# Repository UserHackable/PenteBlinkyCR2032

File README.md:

## PentaBlinkyCR2032 

### Board dimensions

* (130000, 150000) original units
* (1.3000, 1.5000) inches
* (33.0200, 38.1000) mm

[gerbers](PentaBlinkyCR2032_gerber.zip?raw=true)

| Front | Back |
| --- | --- |
|  |  |

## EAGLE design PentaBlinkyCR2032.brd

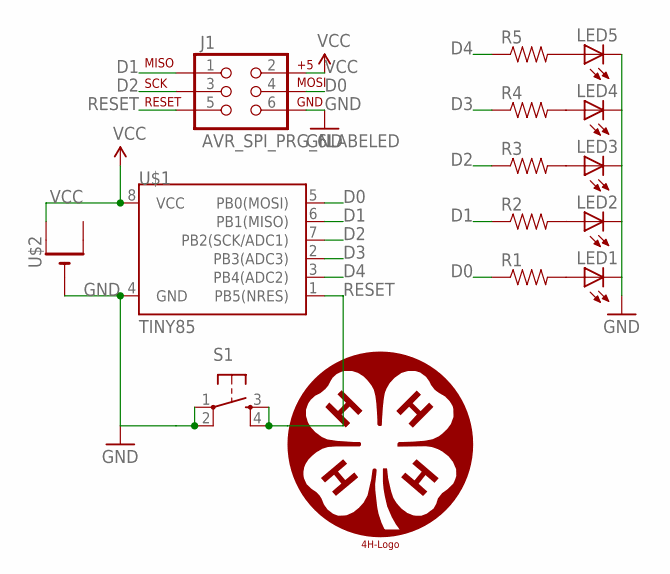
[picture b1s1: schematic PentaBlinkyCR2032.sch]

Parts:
J1: AVR_SPI_PRG_6LABELED; 2X3-NS
LED1, LED2, LED3, LED4, LED5: LED5MM
R1, R2, R3, R4, R5: RESISTORAXIAL-0.3; AXIAL-0.3
S1: TAC_SWITCHPTH; TACTILE-PTH
U$1: TINY85; DIP08
U$2: CR2032THM; CR2032-THRU
U$4: 4H-LOGO6; 4H_LOGO_6

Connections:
D0: J1.4 (MOSI), R1.P$1 (1), U$1.5 (PB0(MOSI))
D1: J1.1 (MISO), R2.P$1 (1), U$1.6 (PB1(MISO))
D2: J1.3 (SCK), R3.P$1 (1), U$1.7 (PB2(SCK/ADC1))
D3: R4.P$1 (1), U$1.2 (PB3(ADC3))
D4: R5.P$1 (1), U$1.3 (PB4(ADC2))
GND: J1.6 (GND), LED1.K (C), LED2.K (C), LED3.K (C), LED4.K (C), LED5.K (C), S1.1, S1.2, U$1.4 (GND), U$2.-
unnamed: LED1.A, R1.P$2 (2)
unnamed: LED2.A, R2.P$2 (2)
unnamed: LED3.A, R3.P$2 (2)
unnamed: LED4.A, R4.P$2 (2)
unnamed: LED5.A, R5.P$2 (2)
RESET: J1.5 (RST), S1.3, S1.4, U$1.1 (PB5(NRES))
VCC: J1.2 (V+), U$1.8 (VCC), U$2.+1 (+)

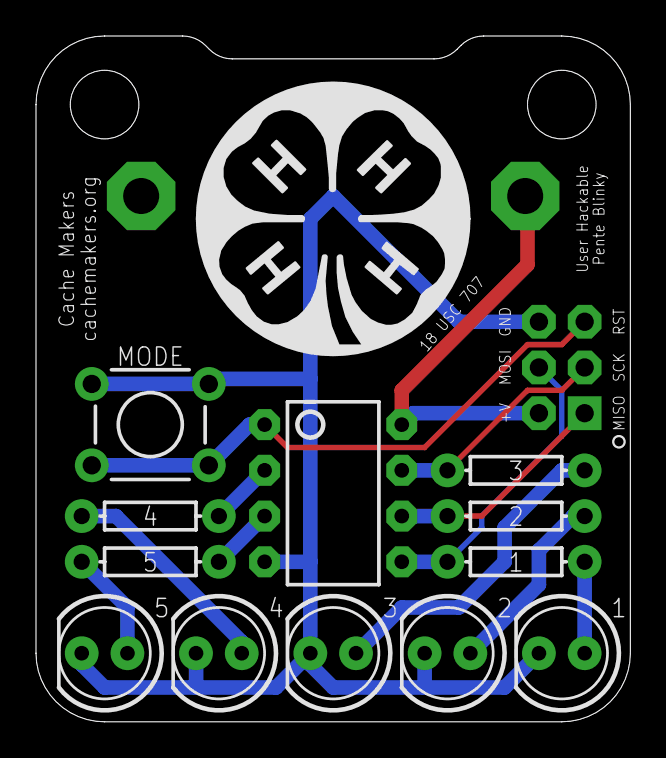
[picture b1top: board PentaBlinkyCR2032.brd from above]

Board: 2 copper layers, 33.0 x 38.1 mm, 15 parts (1 on the bottom side), 13 nets.

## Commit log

2016-04-06 adding images
2016-04-07 4H Branding
2016-04-07 branding for 4h
2016-04-07 from Makefile

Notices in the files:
parts and their libraries:
SparkFun-LED: Licensing: Creative Commons ShareAlike 4.0 International - https://creativecommons.org/licenses/by-sa/4.0
